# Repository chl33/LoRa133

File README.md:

# LoRa133

This project is a base station for LoRa-based satellite sensor devices such as [Garden133](https://github.com/chl33/Garden133).  It includes KiCAD board design and C++ firmware.  LoRa133 allows satellite sensor units to communicate using LoRa radio modules and automatically integrate with Home Assistant.  I build the firmware using the [Platformio](https://platformio.org/) build system.

This is a picture of the base station in its project box in [`OpenSCAD/Lora133/`](OpenSCAD/Lora133/).

This is the PCBA documented in [`KiCAD/LoRa133/`](KiCAD/LoRa133/).

Here is what the web interface (written in Svelte) looks like:

Please see the [Introducing Garden133](https://selectiveappeal.org/posts/garden133/) blog post for more information.

This device uses these libraries:
- [og3](https://github.com/chl33/og3). A basic C++ library for esp development in the Arduino environment.
- [og3x-lora](https://github.com/chl33/og3x-lora). LoRa module support for the og3 library.
- [og3x-satellite](https://github.com/chl33/og3x-satellite). A library that helps build a satellite architecture of a base station and satellite sensors.

## What's New in v0.7.0

*   **Satellite Device Memory**: The bridge now persists its satellite network knowledge across reboots. Restarts no longer result in a blank device list.
*   **Enhanced Visibility**: Real-time RSSI, packet counts, and human-readable "Last Seen" timers added to the web dashboard.
*   **Mobile Optimized**: Fully responsive web interface that fits perfectly on smartphone screens.
*   **og3 v0.6.1 Core**: Modernized backend leveraging the latest declarative dependency and file storage improvements.

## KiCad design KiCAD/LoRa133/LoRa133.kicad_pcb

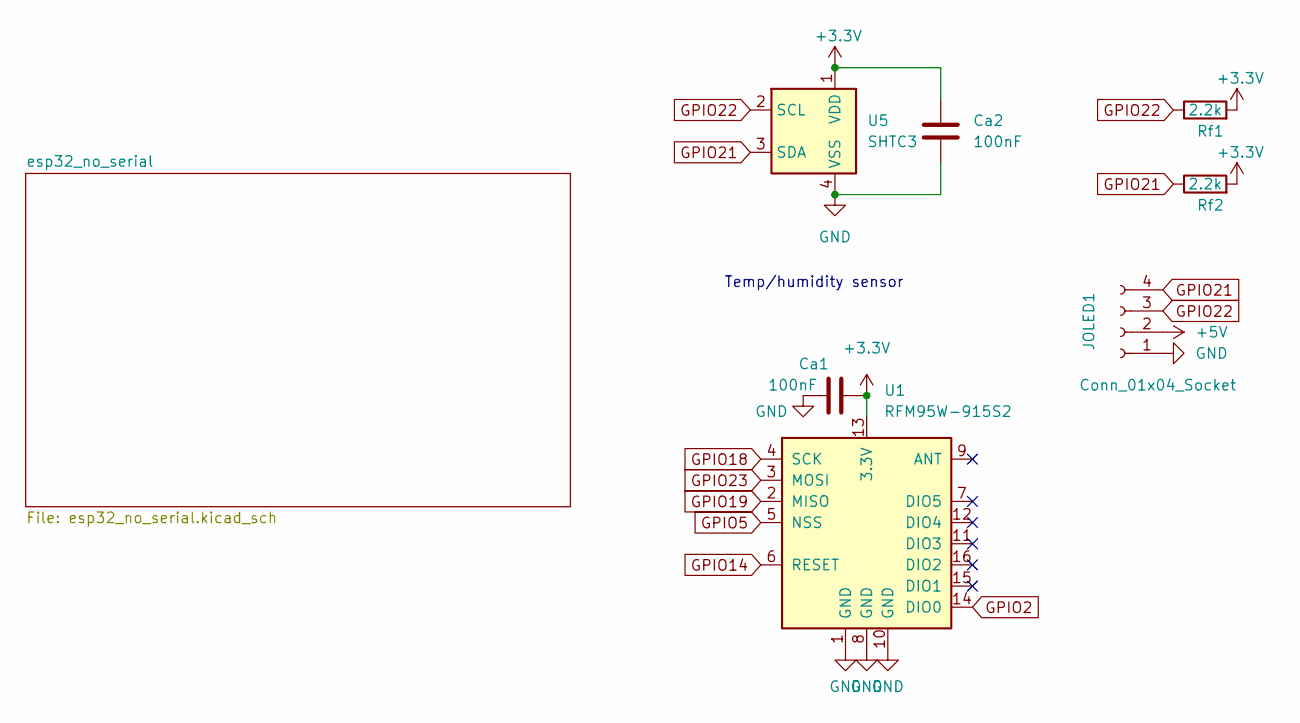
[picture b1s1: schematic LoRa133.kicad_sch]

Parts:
Ca1, Ca2: 100nF; C_0603_1608Metric
JOLED1: Conn_01x04_Socket; PinSocket_1x04_P2.54mm_Vertical
Rf1, Rf2: 2.2k; R_0603_1608Metric
U1: RFM95W-915S2; HOPERF_RFM9XW_SMD
U5: SHTC3; Sensirion_DFN-4-1EP_2x2mm_P1mm_EP0.7x1.6mm

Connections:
+3.3V: Ca1.2, Ca2.1, Rf1.2, Rf2.2, U1.13 (3.3V), U5.1 (VDD); also elsewhere on the board
+5V: JOLED1.2; also elsewhere on the board
GND: Ca1.1, Ca2.2, JOLED1.1, U1.1 (GND), U1.8 (GND), U1.10 (GND), U5.4 (VSS); also elsewhere on the board
GPIO2: U1.14 (DIO0); also elsewhere on the board
GPIO5: U1.5 (NSS); also elsewhere on the board
GPIO14: U1.6 (RESET); also elsewhere on the board
GPIO18: U1.4 (SCK); also elsewhere on the board
GPIO19: U1.2 (MISO); also elsewhere on the board
GPIO21: JOLED1.4, Rf2.1, U5.3 (SDA); also elsewhere on the board
GPIO22: JOLED1.3, Rf1.1, U5.2 (SCL); also elsewhere on the board
GPIO23: U1.3 (MOSI); also elsewhere on the board

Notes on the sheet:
Temp/humidity sensor

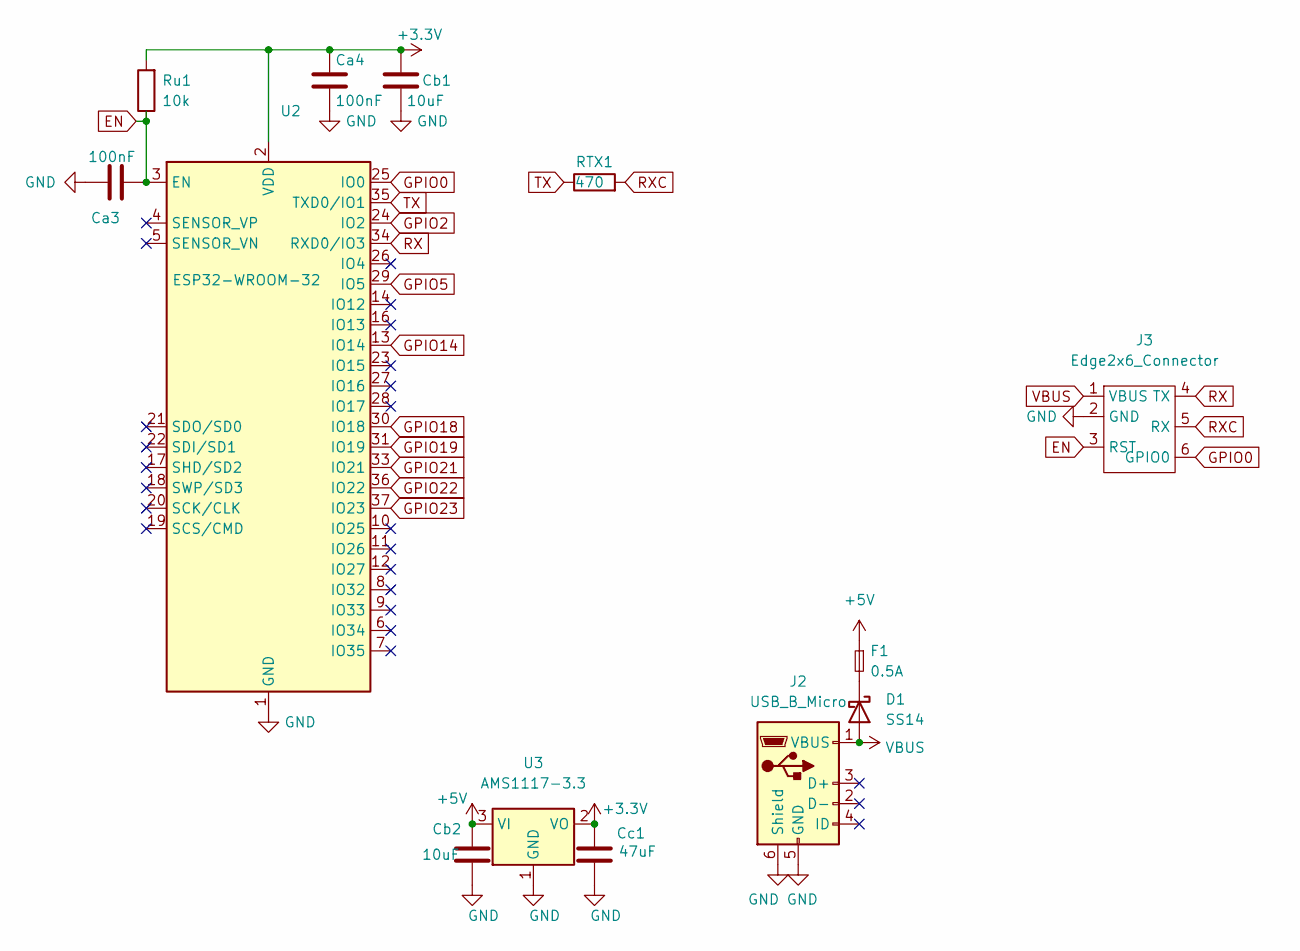
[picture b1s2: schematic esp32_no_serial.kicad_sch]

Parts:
Ca3, Ca4: 100nF; C_0603_1608Metric
Cb1: 10uF; C_0805_2012Metric
Cb2: 10uF; C_0805_2012Metric_Pad1.18x1.45mm_HandSolder
Cc1: 47uF; C_0805_2012Metric_Pad1.18x1.45mm_HandSolder
D1: SS14; D_2010_5025Metric
F1: 0.5A; D_0805_2012Metric
J2: USB_B_Micro; USB_Micro-B_Amphenol_10118194_Horizontal
J3: Edge2x6_Connector; EdgeConnector_2x3
RTX1: 470; R_0603_1608Metric
Ru1: 10k; R_0603_1608Metric
U2: ESP32-WROOM-32
U3: AMS1117-3.3; SOT-223-3_TabPin2

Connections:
+3.3V: Ca4.1, Cb1.1, Cc1.1, Ru1.2, U2.2 (VDD), U3.2 (VO); also elsewhere on the board
+5V: Cb2.1, F1.1, U3.3 (VI); also elsewhere on the board
EN: Ca3.2, J3.3 (RST), Ru1.1, U2.3 (EN)
GND: Ca3.1, Ca4.2, Cb1.2, Cb2.2, Cc1.2, J2.5 (GND), J2.6 (Shield), J3.2 (GND), U2.1 (GND), U2.15 (GND), U2.38 (GND), U2.39 (GND), U3.1 (GND); also elsewhere on the board
GPIO0: J3.6 (GPIO0), U2.25 (IO0)
GPIO2: U2.24 (IO2); also elsewhere on the board
GPIO5: U2.29 (IO5); also elsewhere on the board
GPIO14: U2.13 (IO14); also elsewhere on the board
GPIO18: U2.30 (IO18); also elsewhere on the board
GPIO19: U2.31 (IO19); also elsewhere on the board
GPIO21: U2.33 (IO21); also elsewhere on the board
GPIO22: U2.36 (IO22); also elsewhere on the board
GPIO23: U2.37 (IO23); also elsewhere on the board
unnamed: D1.1 (K), F1.2
RX: J3.4 (TX), U2.34 (RXD0/IO3)
RXC: J3.5 (RX), RTX1.2
TX: RTX1.1, U2.35 (TXD0/IO1)
VBUS: D1.2 (A), J2.1 (VBUS), J3.1 (VBUS)

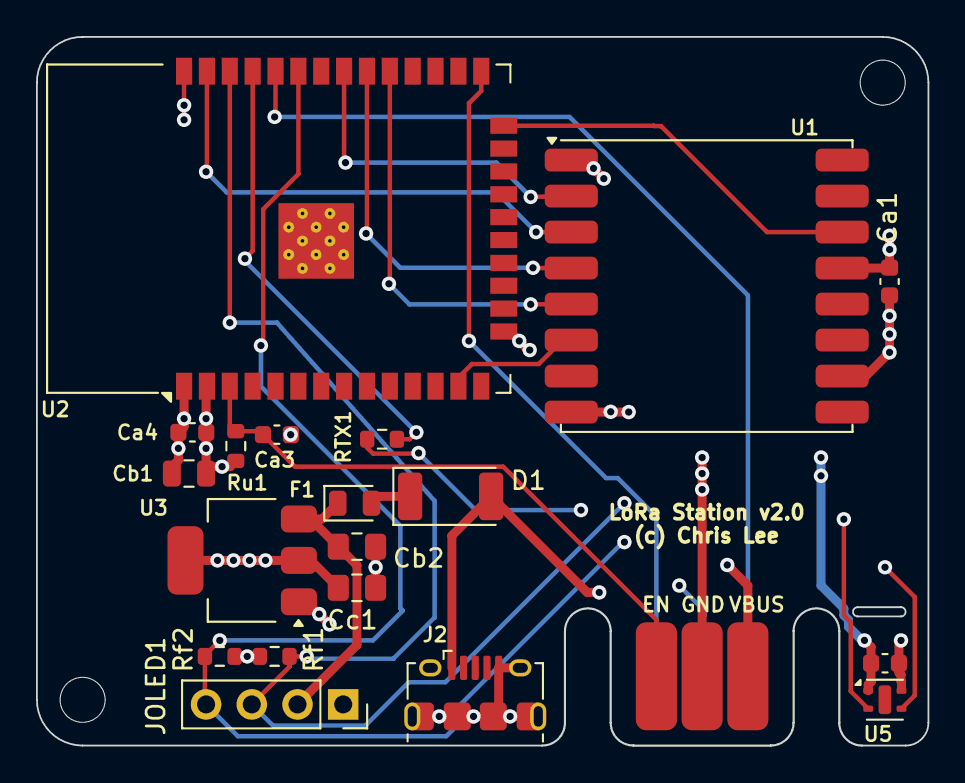
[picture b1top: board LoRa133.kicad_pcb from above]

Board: 4 copper layers, 49.5 x 39.4 mm, 20 parts (0 on the bottom side), 18 nets.

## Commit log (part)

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2025-02-09 initial version -- WIP
2025-02-09 Start of "satellite" sensor/device support.
2025-02-10 Track dropped packets and RSSI for each satellite device.
2025-02-17 Lots of progress
    - Updated PCB design
    - Added draft of EBox design, and support for OLED.
    - OLED display support
2025-02-17 Box update: taller, more antenna space
2025-02-17 Add support for int-sensor, moisture raw-value
2025-02-19 update README, include device_id as part of device-name
2025-02-22 Support HA discovery for satellite sensors
    - Many improvements
    - Depend on newer versions of og3 libraries
    - Use CRC checks on LoRa packets
2025-03-23 Add device name in ha-discovery topic, to avoid conflicts
2025-05-20 Improvements
    - Trying to add RSSI and dropped packets variable for each device
    - Track each kind of packet-parsing error
    - Upgrade og3 version to check packet CRCs
2025-05-25 Improve logging
2025-06-04 Fix entry-name for device rssi and dropped packets
2025-06-04 KiCAD: updated KiCAD version, page size -> US Letter
2025-06-05 Send MQTT packet every 5 minutes. Actually read the SHTC3 sensor.
2025-06-08 Protocol update, use updated og3x-lora
    - LoRa now configurable via web interface
    - Use og3x-satellite for protobuf messages
    - Update to KiCAD
    - OpenSCAD: base-station box: position hole for antenna if it is orthogonal to the board
    edge
    - Add IP address, temp+humidity to OLED display ring.
2025-06-13 Add a web page which allows disabling MQTT for a device.
2025-06-14 Support sensor state_class for HA long-term statistics
2025-06-14 use published libraries
2025-06-14 KiCAD cache update
2025-06-15 prepare readme
2025-06-15 update license
2025-06-19 Base station library moved to og3x-satellite
2025-06-19 Don't send a device class when sensor type is unspecified
2025-06-19 add example secrets file
2025-06-19 add usb example secrets file
2025-06-19 fix filename
2025-06-19 add upload protocol
2025-06-19 add upload port (IP addr)
2025-06-19 add upload auth
2025-06-19 base station update (#1)
    - Base station library moved to og3x-satellite
    - Don't send a device class when sensor type is unspecified
2025-07-05 remove obsolete library
2025-07-05 version -> 0.4.3
    - fix lora-config web page
    - option to disable new devices by default (useful for dev)
2025-07-05 version 0.4.3 (#2)
    - fix lora-config web page
    - option to disable new devices by default (useful for dev)
    - remove obsolete library
2025-07-07 Update README (#3)
2025-07-19 version 0.5.0
    - Use updated og3x-satellite library for protocol update
    - Use device name directly from satellite protobuf as HA discovery device name
    - Use new device_type as model in HA device
2025-07-19 version 0.5.0 (#4)
    - Use updated og3x-satellite library for protocol update
    - Use device name directly from satellite protobuf as HA discovery device name
    - Use new device_type as model in HA device
2025-08-03 version -> 0.5.1 og3x-satellite upgrade
2025-08-03 version -> 0.5.1 og3x-satellite upgrade (#5)
2025-08-08 version 0.1.5: set readings failed before parsing LoRa packet
    This keeps value not in LoRa packets out of MQTT messages.
2025-08-08 version 0.1.5: set readings failed before parsing LoRa packet (#6)
    This keeps value not in LoRa packets out of MQTT messages.
2025-08-24 upgrade og3 to version 0.3.90
2026-03-22 updates for og3 0.5.0, og3x-lora 0.6.0 (gemini)
2026-03-22 license header updates
2026-03-22 Gemini created a Svelte interface (untested)
2026-03-22 got (cd svelte; npm run dev) to work (gemini)
2026-03-22 radio theme (clean-up plant/garage stuff)
2026-03-22 update platformio board environments
2026-03-22 gemini fixes
2026-03-22 software version -> 0.6.0
2026-03-23 more compact layout of readings
2026-03-28 Fix restart button, initial support for device comms time-out.
2026-03-28 Gemini updates to interface: online/offline, mobile layout
2026-03-28 update device_Type info in packets
2026-03-28 show more device comms stats
2026-03-28 check for other things that might be updated
2026-03-28 Version info in interface, fix loading devices from flash.
2026-03-29 Request saving devices new sensors are added.
2026-03-29 dependabot
2026-03-29 fix "Last Seen" on web page when device is not yet seen
2026-03-29 Software version -> 0.7.0
2026-03-29 REAME and CHANGELOG (gemini)
2026-03-29 show web UI
2026-03-29 updated example local.ini and secrets.ini
2026-03-29 update deps to be published versions
2026-03-29 shrink web image
2026-03-29 update deps and workflow-build
2026-03-29 fix workflow
2026-03-29 version 0.7.0 (#7)
    ### Added
    - **Satellite Persistence**: Implemented full persistence for the satellite network. The bridge now "remembers" all known devices and their sensor configurations across reboots by storing them in fla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
    - **Cold-Start Parsing**: The bridge can now parse sensor data packets immediately after a reboot without waiting for a device description packet, thanks to restored sensor metadata.
    - **Dynamic Metadata Sync**: Added support for updating device names, manufacturer IDs, and firmware versions as they arrive in LoRa packets.
    - **Enhanced Telemetry**: Added RSSI, packet count, and human-readable "Last Seen" timers to the web interface.
    - **Mo
2026-03-29 Bump actions/setup-node from 4 to 6
    Bumps [actions/setup-node](https://github.com/actions/setup-node) from 4 to 6.
    - [Release notes](https://github.com/actions/setup-node/releases)
    - [Commits](https://github.com/actions/setup-node/compare/v4...v6)
    ---
    updated-dependencies:
    - dependency-name: actions/setup-node
2026-03-29 Bump actions/cache from 4 to 5
    Bumps [actions/cache](https://github.com/actions/cache) from 4 to 5.
    - [Release notes](https://github.com/actions/cache/releases)
    - [Changelog](https://github.com/actions/cache/blob/main/RELEASES.md)
    - [Commits](https://github.com/actions/cache/compare/v4...v5)
    ---
    updated-dependencies:
2026-03-29 Bump actions/setup-python from 5 to 6
    Bumps [actions/setup-python](https://github.com/actions/setup-python) from 5 to 6.
    - [Release notes](https://github.com/actions/setup-python/releases)
    - [Commits](https://github.com/actions/setup-python/compare/v5...v6)
    ---
    updated-dependencies:
    - dependency-name: actions/setup-python
2026-03-29 Bump actions/checkout from 4 to 6
    Bumps [actions/checkout](https://github.com/actions/checkout) from 4 to 6.
    - [Release notes](https://github.com/actions/checkout/releases)
    - [Changelog](https://github.com/actions/checkout/blob/main/CHANGELOG.md)
    - [Commits](https://github.com/actions/checkout/compare/v4...v6)
    ---
    updated-dependencies:
2026-06-18 Bump actions/checkout from 4 to 7
    Bumps [actions/checkout](https://github.com/actions/checkout) from 4 to 7.
    - [Release notes](https://github.com/actions/checkout/releases)
    - [Changelog](https://github.com/actions/checkout/blob/main/CHANGELOG.md)
    - [Commits](https://github.com/actions/checkout/compare/v4...v7)
    ---
    updated-dependencies:
2026-06-23 Bump actions/cache from 4 to 6
    Bumps [actions/cache](https://github.com/actions/cache) from 4 to 6.
    - [Release notes](https://github.com/actions/cache/releases)
    - [Changelog](https://github.com/actions/cache/blob/main/RELEASES.md)
    - [Commits](https://github.com/actions/cache/compare/v4...v6)
    ---
    updated-dependencies:
